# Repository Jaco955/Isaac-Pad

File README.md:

# Isaac-Pad
A macro pad made entirely to play The BInding of Isaac and similar indie games, made by following the Stardance tutorial.

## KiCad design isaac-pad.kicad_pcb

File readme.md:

# Isaac Pad

A custom 12-key macropad designed for gaming indie games that require 12 keys or less to be properly enjoyed.

## Specifications

- Microcontroller: Seeed XIAO RP2040
- 12 MX-style mechanical switches
- Matrix: 4 rows x 3 columns
- Firmware: QMK
- 12 diodes

## Features

- Custom-designed PCB
- Custom 3D-printed enclosure
- 12 programmable mechanical keys
- QMK Firmware
- Compact and real sleek design

## Design files
This repository includes:
- Kicad PCB files(inside of hardware/pcb)
- Gerber manufacturing files(inside of hardware/pcb)
- 3d models(inside of hardware/case)
- STEP assembly model(inside of hardware/case)
- Bill of materials (inside documentation folder)
## Schematic for PCB 

## PCB

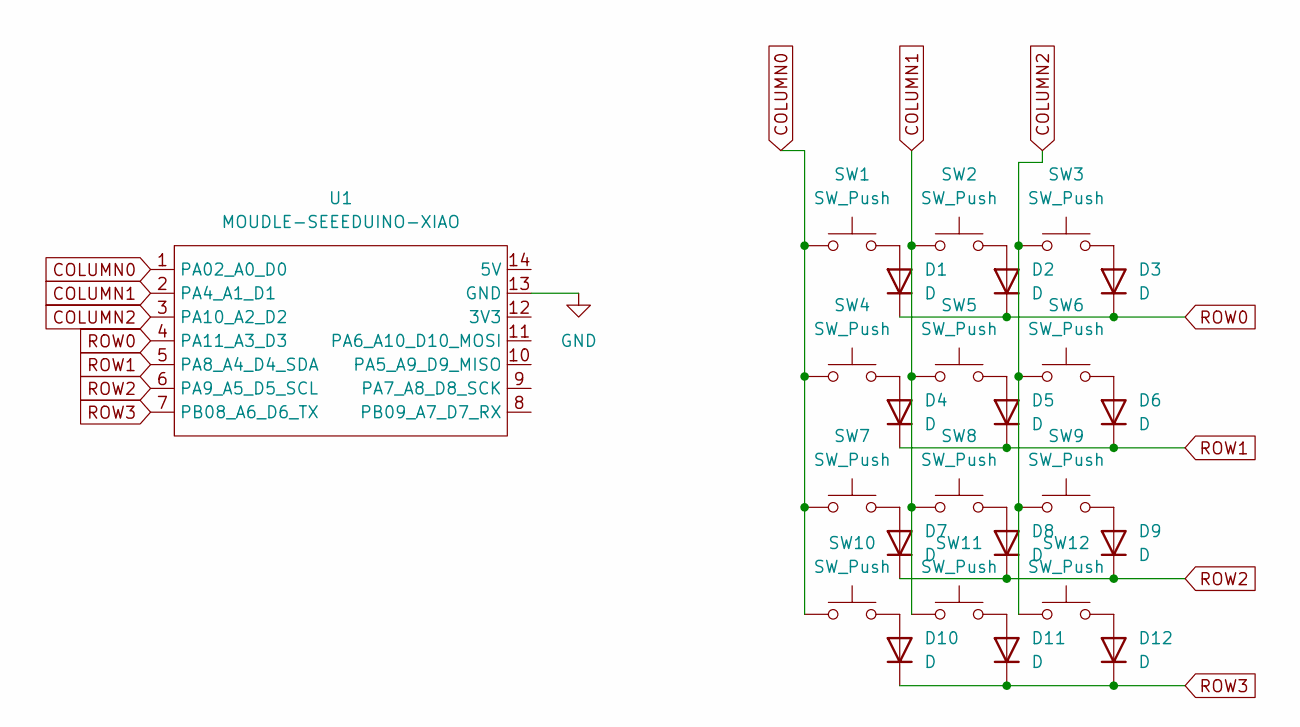
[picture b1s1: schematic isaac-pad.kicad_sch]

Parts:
D1, D2, D3, D4, D5, D6, D7, D8, D9, D10, D11, D12: D; D_DO-35_SOD27_P7.62mm_Horizontal
SW1, SW2, SW3, SW4, SW5, SW6, SW7, SW8, SW9, SW10, SW11, SW12: SW_Push; SW_Cherry_MX_1.00u_PCB
U1: MOUDLE-SEEEDUINO-XIAO; XIAO-Generic-Hybrid-14P-2.54-21X17.8MM

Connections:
COLUMN0: SW1.1, SW4.1, SW7.1, SW10.1, U1.1 (PA02_A0_D0)
COLUMN1: SW2.1, SW5.1, SW8.1, SW11.1, U1.2 (PA4_A1_D1)
COLUMN2: SW3.1, SW6.1, SW9.1, SW12.1, U1.3 (PA10_A2_D2)
GND: U1.13 (GND)
unnamed: D1.2 (A), SW1.2
unnamed: D2.2 (A), SW2.2
unnamed: D3.2 (A), SW3.2
unnamed: D4.2 (A), SW4.2
unnamed: D5.2 (A), SW5.2
unnamed: D6.2 (A), SW6.2
unnamed: D7.2 (A), SW7.2
unnamed: D8.2 (A), SW8.2
unnamed: D9.2 (A), SW9.2
unnamed: D10.2 (A), SW10.2
unnamed: D11.2 (A), SW11.2
unnamed: D12.2 (A), SW12.2
ROW0: D1.1 (K), D2.1 (K), D3.1 (K), U1.4 (PA11_A3_D3)
ROW1: D4.1 (K), D5.1 (K), D6.1 (K), U1.5 (PA8_A4_D4_SDA)
ROW2: D7.1 (K), D8.1 (K), D9.1 (K), U1.6 (PA9_A5_D5_SCL)
ROW3: D10.1 (K), D11.1 (K), D12.1 (K), U1.7 (PB08_A6_D6_TX)

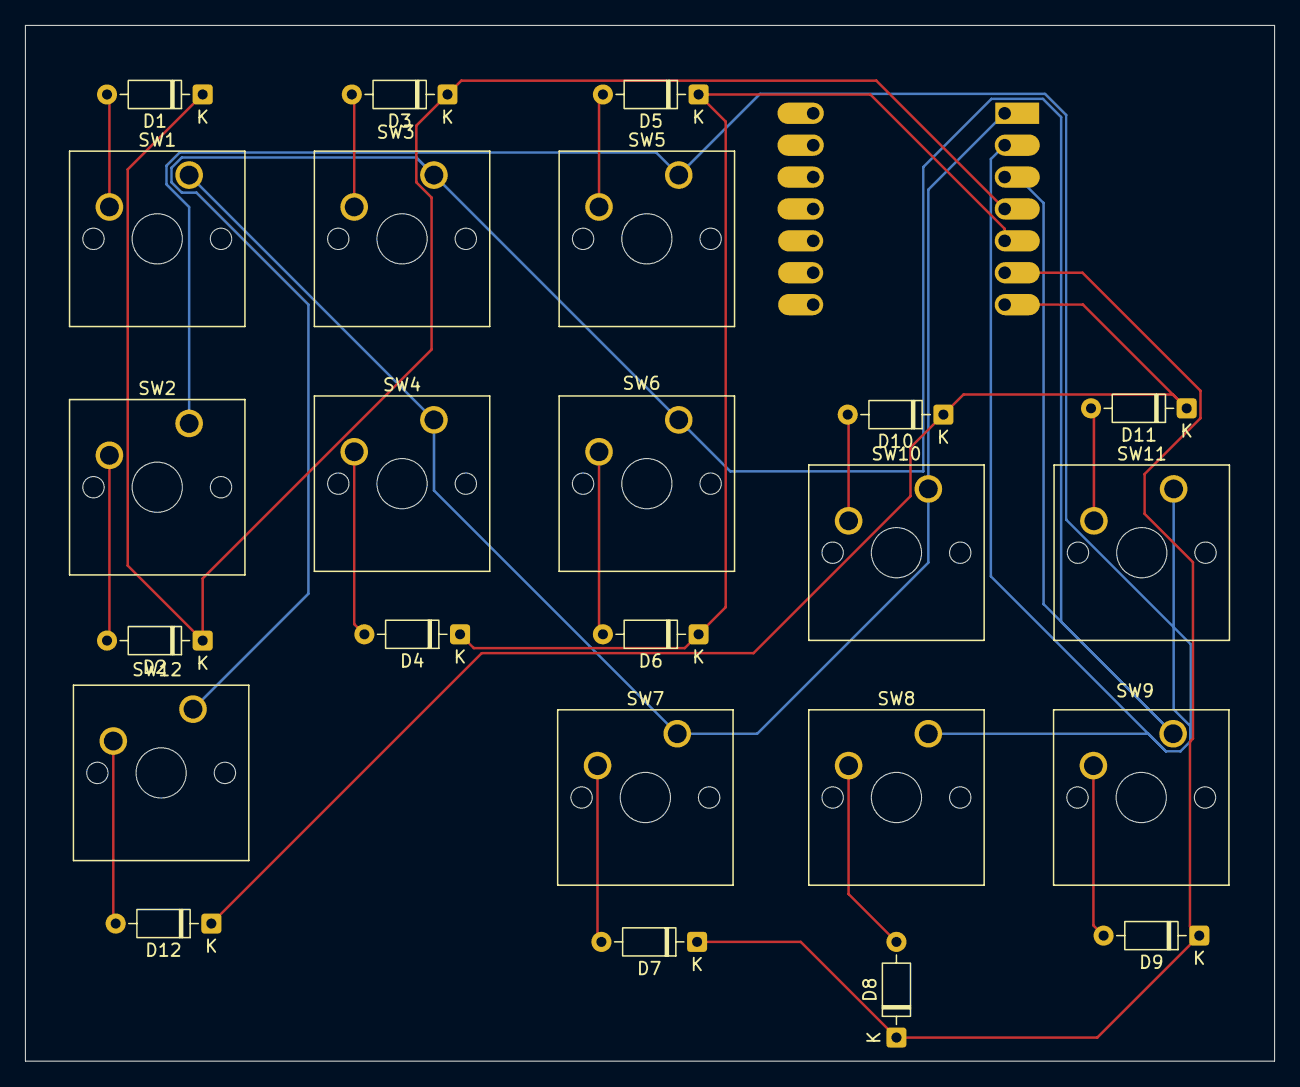
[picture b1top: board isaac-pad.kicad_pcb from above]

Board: 2 copper layers, 99.5 x 82.5 mm, 25 parts (1 on the bottom side), 19 nets.
